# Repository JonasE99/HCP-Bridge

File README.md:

# HCP-Bridge – Hörmann series 4 garage doors on Wi-Fi / Loxone

> **⚠ Work in progress – rev 0.1 has not been manufactured or tested yet.**
> Schematic and layout are complete and checked (ERC 0 errors, DRC 0 errors), but no board has
> been built or run on an operator so far. Build at your own risk; results of the first build
> will be added here.

A small board (one per door) that plugs into the **BUS port** (RJ12) of a Hörmann series 4
garage door operator (ProMatic 4, SupraMatic E/P 4). It acts as a UAP1-HCP expansion module
towards the operator and exposes the door via Wi-Fi. Loxone talks to it over plain HTTP, no
extra server needed (see below).

**Firmware:** This repository contains the hardware only. The board is meant to run the existing
third-party open-source firmware **[HCPBridgeMqtt by Gifford47](https://github.com/Gifford47/HCPBridgeMqtt)**
(environment `HCP_Giffordv2`, provides web UI, HTTP API and MQTT). The board uses the same pins
as the original ESP32-S3 boards, so the firmware runs unchanged. Please direct firmware questions
to that project.

**Status rev 0.1 (2026-10-14):** ERC 0 errors, DRC 0 errors (4 warnings: footprint silkscreen at
the board edge, trimmed by the manufacturer).

## Key data

| | |
|---|---|
| Size | 36 × 72 mm, 2 layers, 1.6 mm, 2 × M3 |
| Power | from the bus (24 V, approx. 20–40 mA) or USB-C (5 V) |
| Radio | ESP32-S3-WROOM-1-N8R2 (PCB antenna at the top edge, no copper underneath) |
| RS-485 | TI THVD1406, automatic direction control via TX (the firmware uses TX/RX only) |
| Protection | 200 mA PTC fuse, TVS SMAJ33CA, SM712 + 10 Ω on A/B, ESD protection on USB |
| Regulator | TI LMR51610 (4–65 V, 1 A) to 3.3 V, laid out following the TI layout guidelines |
| Pins | RS-485 TX = GPIO17, RX = GPIO18, status LED = GPIO13 (as `HCP_Giffordv2`) |

### Reverse polarity and cable tolerant

RJ12 cables exist as straight and crossed versions, and the pin 1 side of the jack was derived
from documentation. Reversed, +24 V would end up on GND and A/B would be swapped. Therefore:
- Power goes through a **bridge rectifier** (4 × Schottky): polarity does not matter and the
  board is not damaged either way.
- **Solder jumpers A/B** (JP1/JP2), default 1-2 (A = jack pin 4, B = pin 3).
- **JP3 "120R"** (bus termination): leave open, close only if communication is unreliable.

**Setting A/B – one measurement is enough:** cable and jack can only swap the wires mirrored
(1↔6, 2↔5, 3↔4), so power and data always flip together. With the bridge plugged in and the
operator powered, measure on the **bottom side at the solder pins of the RJ12 jack J1**: red probe
on the pin marked **"+"** (pin 5, outer pin), black probe on the pin marked **"−"** (pin 1, outer
pin on the other end):

| Reading at J1 (+ against −) | JP1 and JP2 |
|---|---|
| approx. **+24 V** | keep at **1-2** (default) |
| approx. **−24 V** | resolder **both to 2-3** |

The rule is also printed on the bottom side. Bus pinout at the operator according to
HCPBridgeMqtt: 1/2 GND, 3 B−, 4 A+, 5/6 +24 V.

## Folders

```
hardware/kicad/        KiCad 9 project HCPBridge.kicad_pro (schematic, PCB, own footprints)
hardware/fabrication/  schematic PDF, Gerber ZIP, BOM, LCSC order file, JLCPCB BOM + CPL, assembly drawing, ERC/DRC
docs/                  board render
```

## Ordering (2 doors → 2 boards, plan a spare)

- **PCB:** upload `hardware/fabrication/HCPBridge-gerber.zip` to JLCPCB (2 layers, 1.6 mm,
  lead-free HASL; 5 pcs is the minimum).
- **Parts:** at [lcsc.com](https://www.lcsc.com) open **BOM Tool → Upload BOM File** and upload
  `hardware/fabrication/lcsc-order.xlsx` (or `lcsc-order.csv`). When asked to assign the columns,
  choose `LCSC Part Number` → LCSC Part Number and `Quantity` → Quantity. **`Quantity` is the
  quantity per board**; enter the number of boards (e.g. 3 = 2 doors + 1 spare) as the order
  multiplier in the BOM tool. The column `Total for 3 boards + spare` is for checking only (it
  adds 5 spare pieces of each small 0603 part, which tend to get lost when hand soldering), do
  not assign it. LCSC rounds up to its minimum order quantities. `bom.csv` is the per-board list
  with reference designators. Solder jumpers and test points are copper only.
- **JLCPCB assembly (alternative to hand soldering):** upload `jlcpcb-bom.csv` (BOM) and
  `jlcpcb-cpl.csv` (pick and place) in the PCB assembly step. Rotations and reference points were
  derived from the LCSC/EasyEDA footprints. Check D8, F1, L1 and U1 in the JLC placement preview:
  their EasyEDA data could not be compared (pin 1 of D8/U1 must match the marking on the board).
  J1 (RJ12) is a through-hole part; select it only if you also order through-hole assembly.
- **Optional:** order a stencil from JLCPCB as well, it makes USB-C and the ESP32 module much
  easier.
- **Cable:** RJ12 6P6C cable with **all 6 wires populated** (many phone cables only have 4!).
  Straight or crossed does not matter, the solder jumpers take care of it.

## Assembly and first start

1. Populate the regulator first (U1, L1, C1–C5, R1–R4, D7) and power it from USB-C: green LED on,
   3.3 V across C4. Then the rest. Assembly drawing: `hardware/fabrication/assembly.pdf`.
2. Flash the firmware with PlatformIO (guide:
   [flashing_instructions.md](https://github.com/Gifford47/HCPBridgeMqtt/blob/master/docs/flashing_instructions.md)),
   environment **`HCP_Giffordv2`** (ESP32-S3, TX 17 / RX 18, LED 13, PSRAM). Connect USB-C to the
   PC; if the ESP32 is not detected: hold BOOT, press RESET.
3. The bridge opens a hotspot; enter your Wi-Fi at `http://192.168.4.1`, then assign a **fixed
   IP** in your router. Set a password in the web UI (see Loxone).
4. **Unplug USB**, plug the bridge into the BUS port of the operator with the RJ12 cable.
5. **Measure at J1** (bottom side, "+"/"−") and set the A/B jumpers accordingly (see above).
   Unplug the RJ12 cable before resoldering.
6. Start a **bus scan** on the operator (otherwise it does not see the bridge): depending on the
   control board via menu 37 or by switching the last DIP switch ON → OFF. Guide:
   [bus_scan_EN.md](https://github.com/Gifford47/HCPBridgeMqtt/blob/master/docs/bus_scan_EN.md).
   The door state must then show up in the web UI.

Do not connect USB (PC) and the bus at the same time if PC and operator are earthed differently.

## Loxone integration (HTTP, no MQTT)

The commands are simple GET requests. With a web password set, the bridge asks for basic auth
(user `admin`); in Loxone use the address `http://admin:<password>@<ip>`.

**Virtual output** "Garage door 1", address `http://admin:<pw>@192.168.x.y`, commands:

| Command | Request on ON |
|---|---|
| Open | `/command?action=1` |
| Close | `/command?action=0` |
| Stop | `/command?action=2` |
| Toggle (impulse) | `/command?action=8` |
| Half open | `/command?action=4` |
| Venting | `/command?action=3` |
| Toggle light | `/command?action=5` |
| Position (0–100) | `/command?action=7&position=<v>` (analog) |

**Virtual HTTP input** "Garage door 1 status", URL `http://admin:<pw>@192.168.x.y/status`, polling
every 2–5 s. Command recognition:

| Value | Command recognition | Meaning |
|---|---|---|
| Position | `"currentPosition":\v` | 0 = closed … 100 = open |
| State | `"state":\v` | 0 open, 1 opening, 2 closed, 3 closing, 4 half open, 5/6 venting, 7 moving to half, 8 stopped |
| Light | `"light":\v` | 1 = on (true) |
| Bus OK | `"valid":\v` | 1 = operator responds |

**Gate block:** set the Loxone "Gate" block to "subsequent control" and connect its outputs Op/Cl
(or Tg) to the Open/Close (or Toggle) commands of the virtual output. Feedback comes from the HTTP
input: end position open = state 0, end position closed = state 2, the position directly from
`currentPosition` / 100. The exact inputs and outputs of the block are described in the Loxone
documentation: <https://www.loxone.com/enen/kb/gate/>. Please double-check in Loxone Config; this
mapping has not been tested on a real Miniserver yet.

## Credits and sources

- Firmware and protocol: [Gifford47/HCPBridgeMqtt](https://github.com/Gifford47/HCPBridgeMqtt),
  [Tysonpower/HCPBridgeMqtt_tynet](https://github.com/Tysonpower/HCPBridgeMqtt_tynet)
- Datasheets: [THVD1406](https://www.ti.com/lit/ds/symlink/thvd1406.pdf),
  [LMR51610](https://www.ti.com/lit/ds/symlink/lmr51610.pdf)
- RJ12 hole pattern (Molex 95501-2661): taken from the Gerber files of the board by vladimirzrnic
  in the HCPBridgeMqtt repository (`docs/PCB/vladimirzrnic`)

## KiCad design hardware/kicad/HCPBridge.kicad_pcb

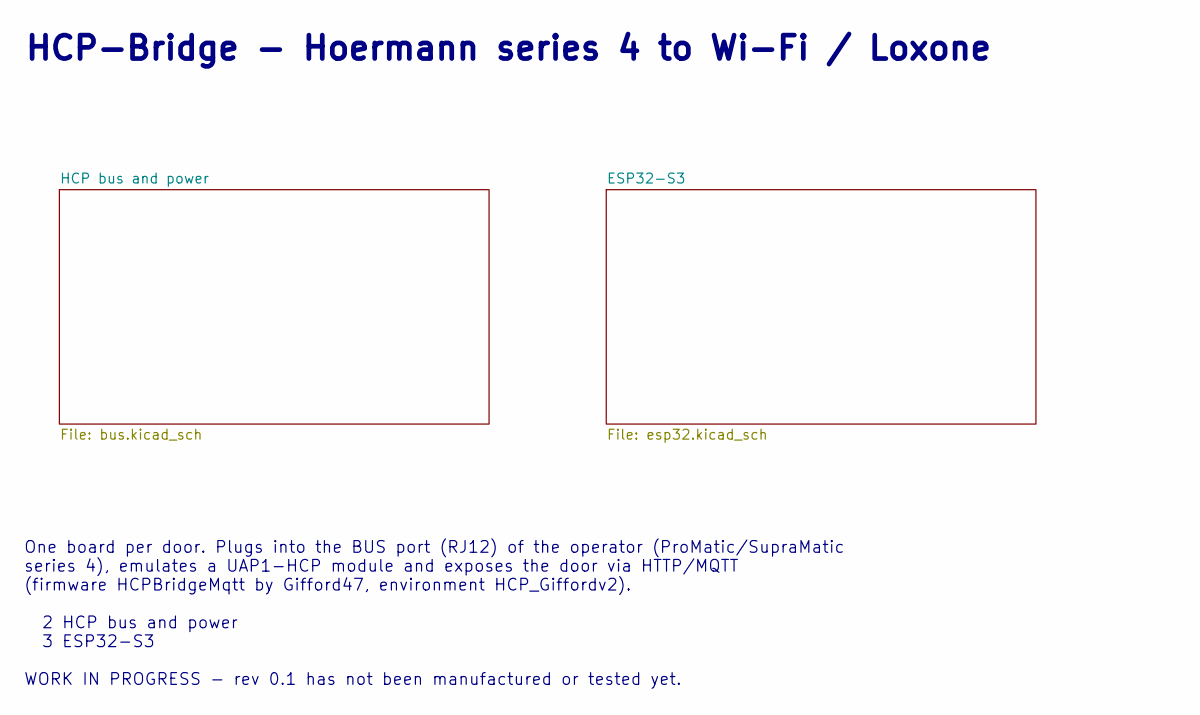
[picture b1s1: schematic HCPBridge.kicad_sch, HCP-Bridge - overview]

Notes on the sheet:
HCP-Bridge - Hoermann series 4 to Wi-Fi / Loxone
One board per door. Plugs into the BUS port (RJ12) of the operator (ProMatic/SupraMatic series 4), emulates a UAP1-HCP module and exposes the door via HTTP/MQTT (firmware HCPBridgeMqtt by Gifford47, environment HCP_Giffordv2). 2 HCP bus and power 3 ESP32-S3 WORK IN PROGRESS - rev 0.1 has not been m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

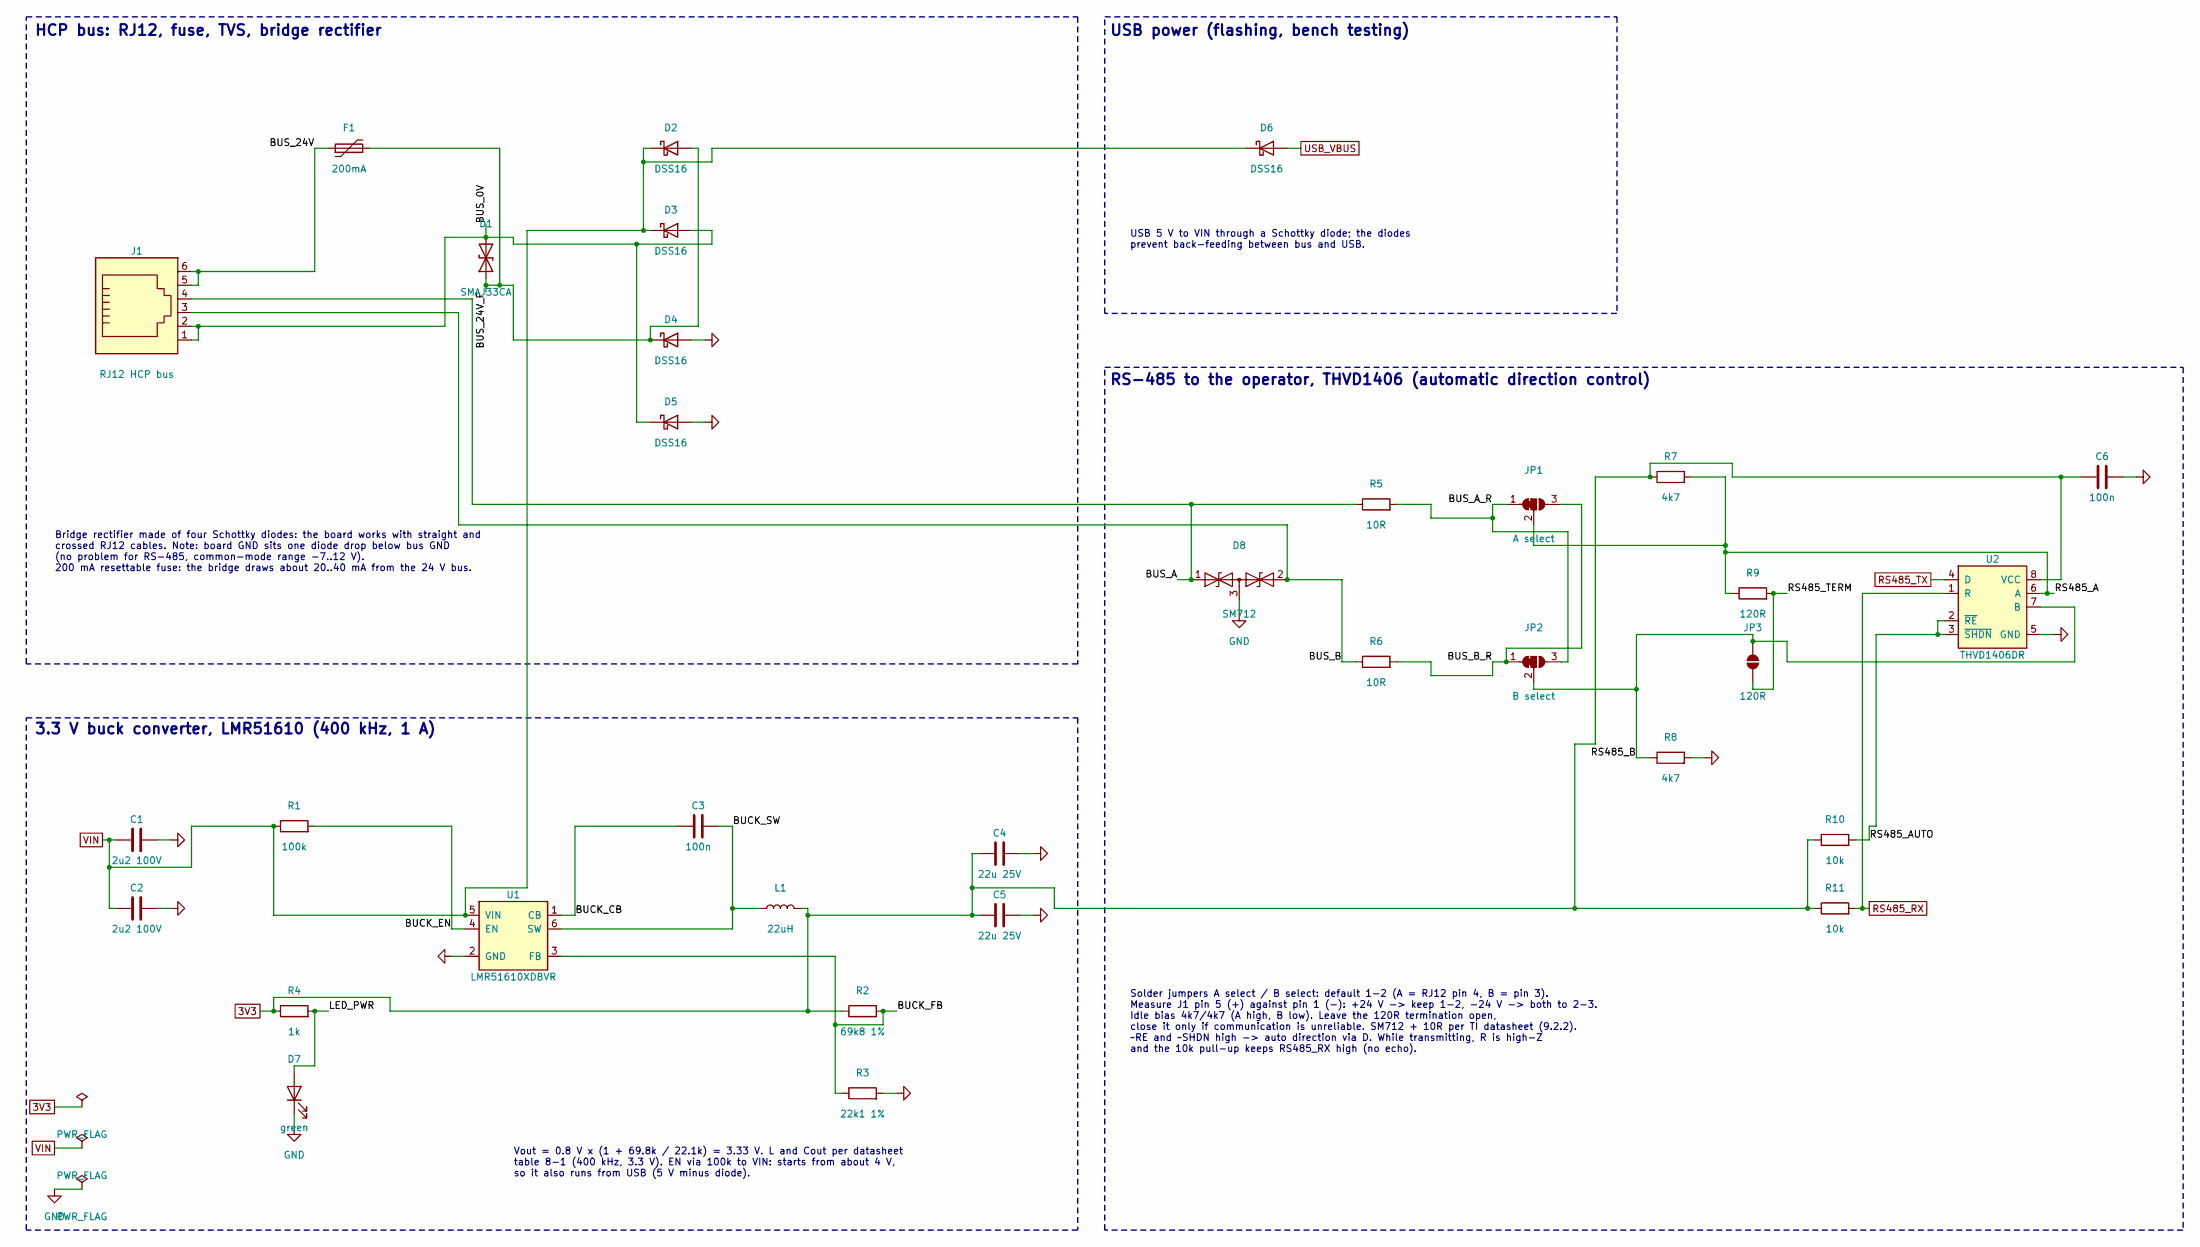
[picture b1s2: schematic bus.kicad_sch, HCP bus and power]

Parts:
C1, C2: 2u2 100V; C_1206_3216Metric; LCSC C170101
C3, C6: 100n; C_0603_1608Metric; LCSC C14663
C4, C5: 22u 25V; C_1206_3216Metric; LCSC C77091
D1: SMAJ33CA; D_SMA; MPN SMAJ33CA (bidirectional); LCSC C115251
D2, D3, D4, D5, D6: DSS16; D_SOD-123; MPN DSS16 (60 V, 1 A); LCSC C7467023
D7: green; LED_0603_1608Metric; MPN KT-0603G; LCSC C12624
D8: SM712; SOT-23; MPN Semtech SM712.TCT; LCSC C12067
F1: 200mA; Fuse_1206_3216Metric; MPN BSMD1206-020-48V; LCSC C49328459
J1: RJ12 HCP bus; RJ12_Molex_95501-2661_Horizontal; MPN Molex 95501-2661; LCSC C240856
JP1: A select; SolderJumper-3_P1.3mm_Bridged12_RoundedPad1.0x1.5mm
JP2: B select; SolderJumper-3_P1.3mm_Bridged12_RoundedPad1.0x1.5mm
JP3: 120R; SolderJumper-2_P1.3mm_Open_RoundedPad1.0x1.5mm
L1: 22uH; L_Sunlord_SWPA5040S; MPN Bourns SRN5040TA-220M (Isat 1.62 A); LCSC C2046438
R1: 100k; R_0603_1608Metric; MPN 0603WAF1003T5E; LCSC C25803
R2: 69k8 1%; R_0603_1608Metric; LCSC C23098
R3: 22k1 1%; R_0603_1608Metric; LCSC C137768
R4: 1k; R_0603_1608Metric; MPN 0603WAF1001T5E; LCSC C21190
R5, R6: 10R; R_0603_1608Metric; LCSC C22859
R7, R8: 4k7; R_0603_1608Metric; MPN 0603WAF4701T5E; LCSC C23162
R9: 120R; R_0603_1608Metric; LCSC C22787
R10, R11: 10k; R_0603_1608Metric; MPN Yageo RC0603FR-0710KL; LCSC C98220
U1: LMR51610XDBVR; SOT-23-6; MPN TI LMR51610XDBVR; LCSC C20539658
U2: THVD1406DR; SOIC-8_3.9x4.9mm_P1.27mm; MPN TI THVD1406DR; LCSC C5215918

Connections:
3V3: C4.1, C5.1, C6.1, L1.2, R2.1, R4.1, R7.1, R10.1, R11.1, U2.8 (VCC); also elsewhere on the board
BUCK_CB: C3.1, U1.1 (CB)
BUCK_EN: R1.2, U1.4 (EN)
BUCK_FB: R2.2, R3.1, U1.3 (FB)
BUCK_SW: C3.2, L1.1, U1.6 (SW)
BUS_0V: D1.2 (A2), D3.2 (A), D5.1 (K), J1.1, J1.2
BUS_24V: F1.1, J1.5, J1.6
BUS_24V_F: D1.1 (A1), D2.2 (A), D4.1 (K), F1.2
BUS_A: D8.1 (A1), J1.4, R5.1
BUS_A_R: JP1.1 (A), JP2.3 (B), R5.2
BUS_B: D8.2 (A2), J1.3, R6.1
BUS_B_R: JP1.3 (B), JP2.1 (A), R6.2
GND: C1.2, C2.2, C4.2, C5.2, C6.2, D4.2 (A), D5.2 (A), D7.1 (K), D8.3 (common), R3.2, R8.2, U1.2 (GND), U2.5 (GND); also elsewhere on the board
LED_PWR: D7.2 (A), R4.2
RS485_A: JP1.2 (C), R7.2, R9.1, U2.6 (A)
RS485_AUTO: R10.2, U2.2 (~RE), U2.3 (~SHDN)
RS485_B: JP2.2 (C), JP3.2 (B), R8.1, U2.7 (B)
RS485_RX: R11.2, U2.1 (R); also elsewhere on the board
RS485_TERM: JP3.1 (A), R9.2
RS485_TX: U2.4 (D); also elsewhere on the board
USB_VBUS: D6.2 (A); also elsewhere on the board
VIN: C1.1, C2.1, D2.1 (K), D3.1 (K), D6.1 (K), R1.1, U1.5 (VIN)

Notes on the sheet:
HCP bus: RJ12, fuse, TVS, bridge rectifier
Bridge rectifier made of four Schottky diodes: the board works with straight and crossed RJ12 cables. Note: board GND sits one diode drop below bus GND (no problem for RS-485, common-mode range -7..12 V). 200 mA resettable fuse: the bridge draws about 20..40 mA from the 24 V bus.
USB power (flashing, bench testing)
USB 5 V to VIN through a Schottky diode; the diodes prevent back-feeding between bus and USB.
3.3 V buck converter, LMR51610 (400 kHz, 1 A)
Vout = 0.8 V x (1 + 69.8k / 22.1k) = 3.33 V. L and Cout per datasheet table 8-1 (400 kHz, 3.3 V). EN via 100k to VIN: starts from about 4 V, so it also runs from USB (5 V minus diode).
RS-485 to the operator, THVD1406 (automatic direction control)
Solder jumpers A select / B select: default 1-2 (A = RJ12 pin 4, B = pin 3). Measure J1 pin 5 (+) against pin 1 (-): +24 V -> keep 1-2, -24 V -> both to 2-3. Idle bias 4k7/4k7 (A high, B low). Leave the 120R termination open, close it only if communication is unreliable. SM712 + 10R per TI datashee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

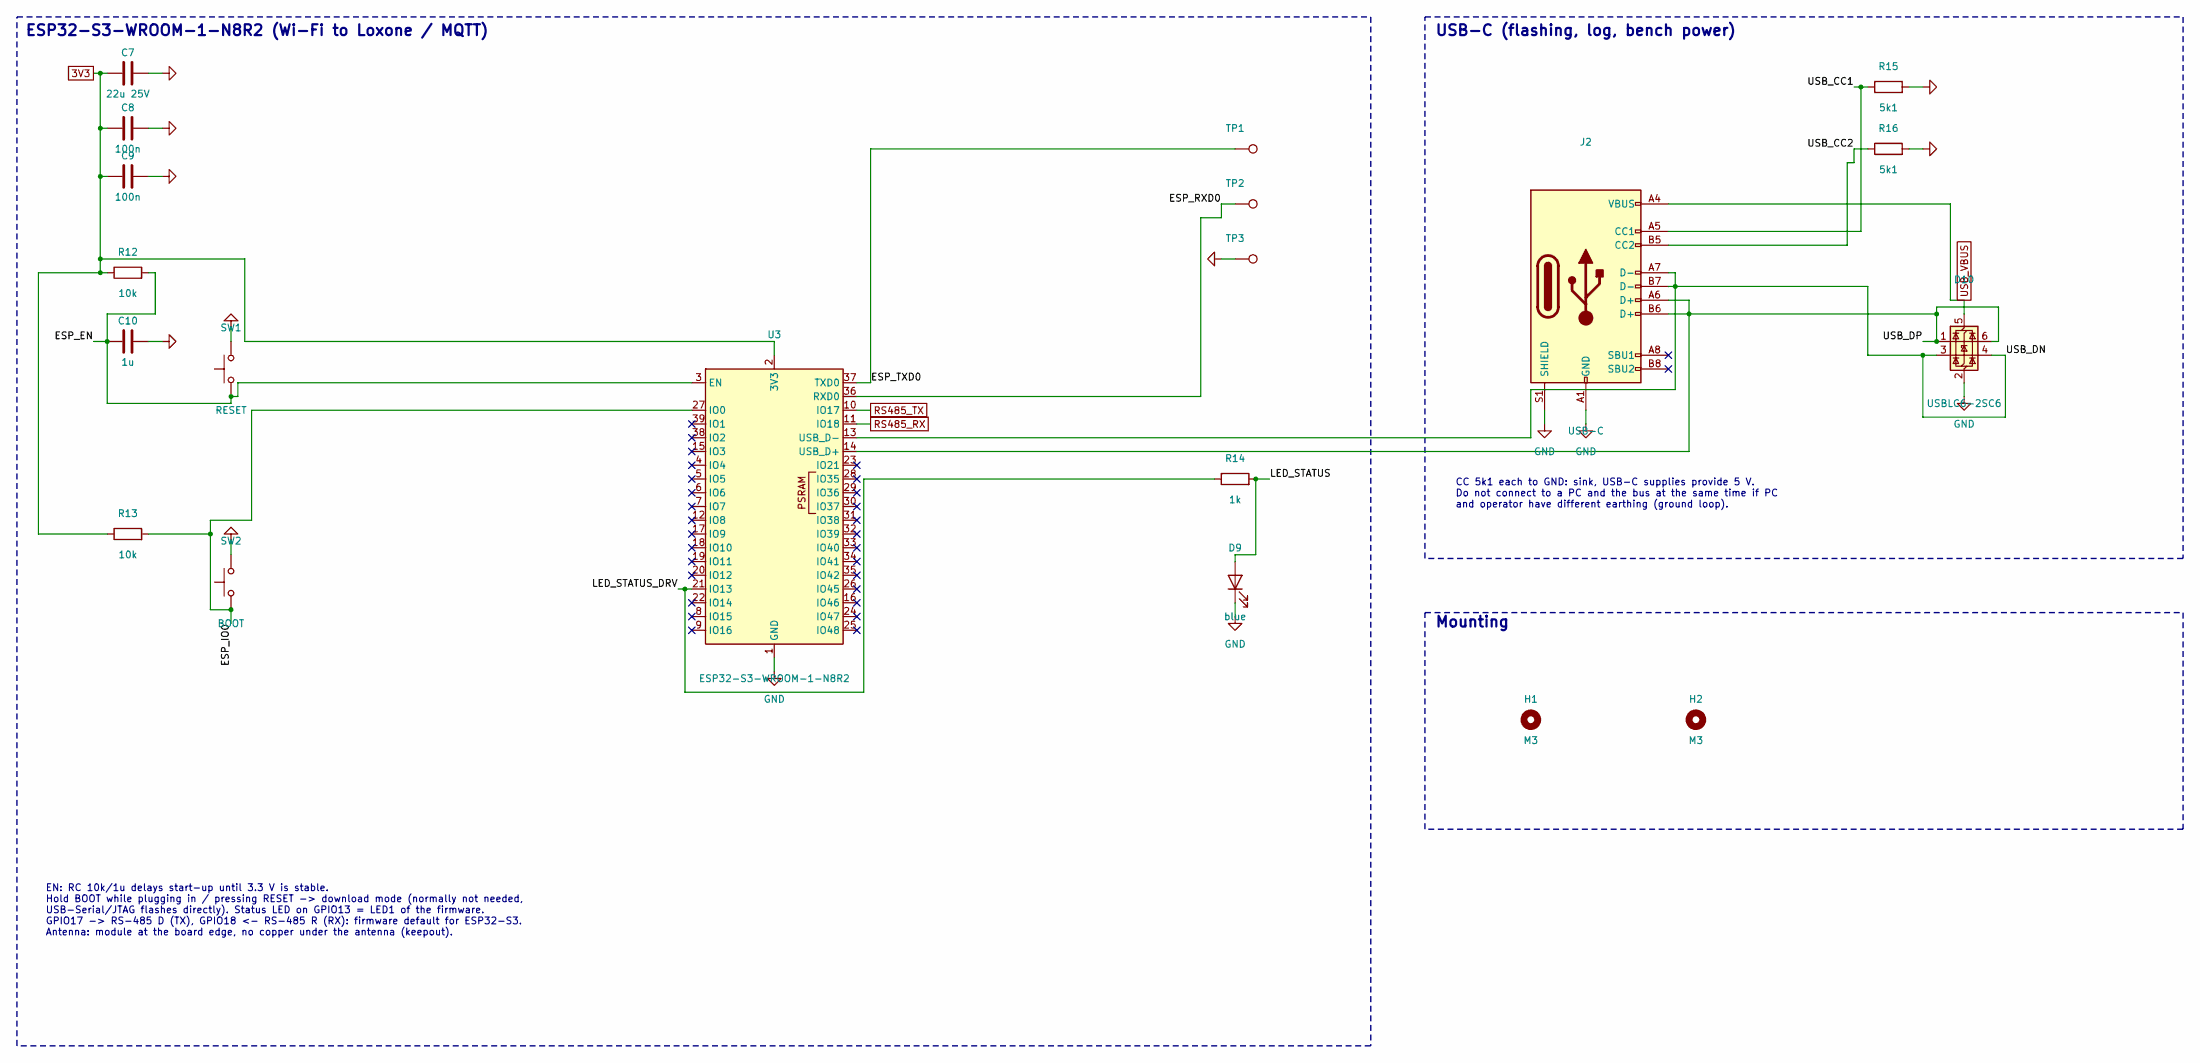
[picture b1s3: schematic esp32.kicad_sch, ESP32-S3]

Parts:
C7: 22u 25V; C_1206_3216Metric; LCSC C77091
C8, C9: 100n; C_0603_1608Metric; LCSC C14663
C10: 1u; C_0603_1608Metric; LCSC C5673
D9: blue; LED_0603_1608Metric; MPN KT-0603B; LCSC C2288
D10: USBLC6-2SC6; SOT-23-6; MPN ST USBLC6-2SC6; LCSC C7519
H1, H2: M3; MountingHole_3.2mm_M3
J2: USB-C; USB_C_Receptacle_HRO_TYPE-C-31-M-12; MPN HRO TYPE-C-31-M-12; LCSC C165948
R12, R13: 10k; R_0603_1608Metric; MPN Yageo RC0603FR-0710KL; LCSC C98220
R14: 1k; R_0603_1608Metric; MPN 0603WAF1001T5E; LCSC C21190
R15, R16: 5k1; R_0603_1608Metric; MPN 0603WAF5101T5E; LCSC C23186
SW1: RESET; SW_Push_1P1T_XKB_TS-1187A; MPN XKB TS-1187A-B-A-B; LCSC C318884
SW2: BOOT; SW_Push_1P1T_XKB_TS-1187A; MPN XKB TS-1187A-B-A-B; LCSC C318884
TP1: ESP_TXD0; TestPoint_Pad_D1.5mm
TP2: ESP_RXD0; TestPoint_Pad_D1.5mm
TP3: GND; TestPoint_Pad_D1.5mm
U3: ESP32-S3-WROOM-1-N8R2; ESP32-S3-WROOM-1; MPN Espressif ESP32-S3-WROOM-1-N8R2; LCSC C2913204

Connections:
3V3: C7.1, C8.1, C9.1, R12.1, R13.1, U3.2 (3V3); also elsewhere on the board
ESP_EN: C10.1, R12.2, SW1.1, U3.3 (EN)
ESP_IO0: R13.2, SW2.1, U3.27 (IO0)
ESP_RXD0: TP2.1, U3.36 (RXD0)
ESP_TXD0: TP1.1, U3.37 (TXD0)
GND: C7.2, C8.2, C9.2, C10.2, D9.1 (K), D10.2 (GND), J2.A1 (GND), J2.A12 (GND), J2.B1 (GND), J2.B12 (GND), J2.S1 (SHIELD), R15.2, R16.2, SW1.2, SW2.2, TP3.1, U3.1 (GND), U3.40 (GND), U3.41 (GND); also elsewhere on the board
LED_STATUS: D9.2 (A), R14.2
LED_STATUS_DRV: R14.1, U3.21 (IO13)
RS485_RX: U3.11 (IO18); also elsewhere on the board
RS485_TX: U3.10 (IO17); also elsewhere on the board
USB_CC1: J2.A5 (CC1), R15.1
USB_CC2: J2.B5 (CC2), R16.1
USB_DN: D10.3 (I/O2), D10.4 (I/O2), J2.A7 (D-), J2.B7 (D-), U3.13 (USB_D-)
USB_DP: D10.1 (I/O1), D10.6 (I/O1), J2.A6 (D+), J2.B6 (D+), U3.14 (USB_D+)
USB_VBUS: D10.5 (VBUS), J2.A4 (VBUS), J2.A9 (VBUS), J2.B4 (VBUS), J2.B9 (VBUS); also elsewhere on the board

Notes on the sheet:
ESP32-S3-WROOM-1-N8R2 (Wi-Fi to Loxone / MQTT)
EN: RC 10k/1u delays start-up until 3.3 V is stable. Hold BOOT while plugging in / pressing RESET -> download mode (normally not needed, USB-Serial/JTAG flashes directly). Status LED on GPIO13 = LED1 of the firmware. GPIO17 -> RS-485 D (TX), GPIO18 <- RS-485 R (RX): firmware default for ESP32-S3. A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
USB-C (flashing, log, bench power)
CC 5k1 each to GND: sink, USB-C supplies provide 5 V. Do not connect to a PC and the bus at the same time if PC and operator have different earthing (ground loop).
Mounting

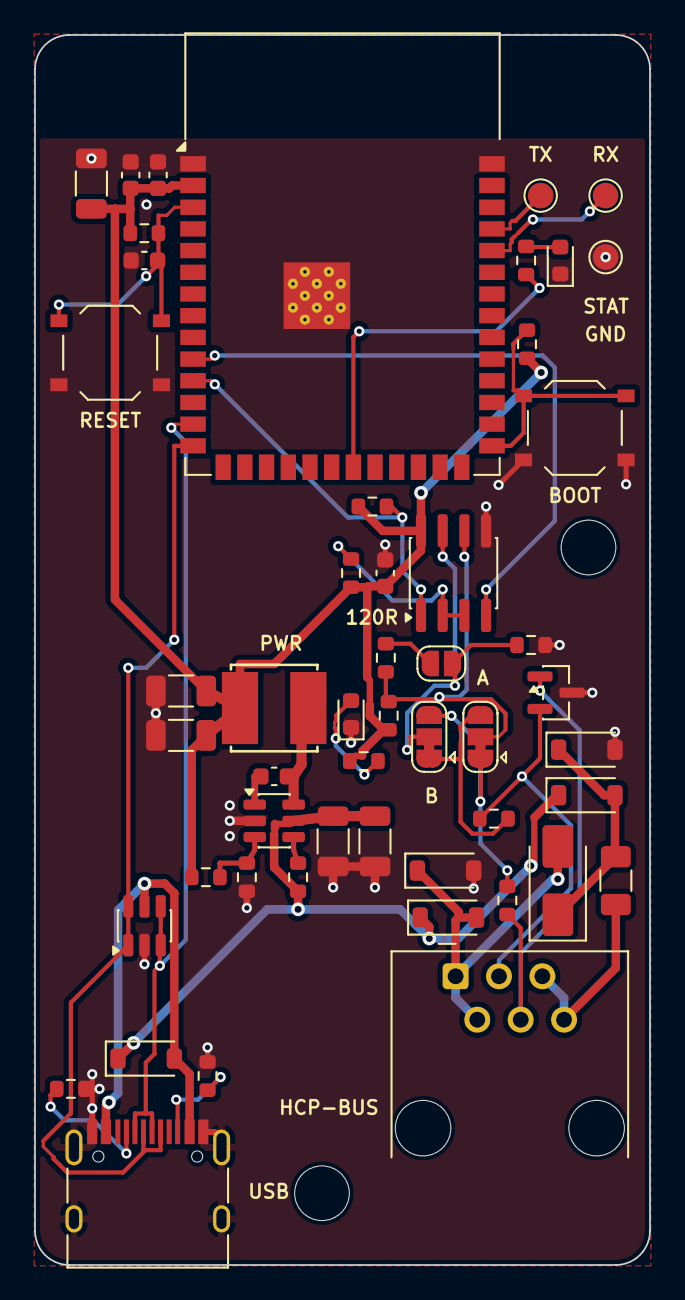
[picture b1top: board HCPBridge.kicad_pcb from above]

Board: 2 copper layers, 36.0 x 72.0 mm, 53 parts (0 on the bottom side), 32 nets.

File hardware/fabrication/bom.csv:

Qty;References;Value;Footprint;Manufacturer part;LCSC
4;C3 C6 C8 C9;100n;C_0603_1608Metric;;C14663
1;C10;1u;C_0603_1608Metric;;C5673
3;C4 C5 C7;22u 25V;C_1206_3216Metric;;C77091
2;C1 C2;2u2 100V;C_1206_3216Metric;;C170101
5;D2 D3 D4 D5 D6;DSS16;D_SOD-123;DSS16 (60 V, 1 A);C7467023
1;D8;SM712;SOT-23;Semtech SM712.TCT;C12067
1;D1;SMAJ33CA;D_SMA;SMAJ33CA (bidirectional);C115251
1;D10;USBLC6-2SC6;SOT-23-6;ST USBLC6-2SC6;C7519
1;D9;blue;LED_0603_1608Metric;KT-0603B;C2288
1;D7;green;LED_0603_1608Metric;KT-0603G;C12624
1;F1;200mA;Fuse_1206_3216Metric;BSMD1206-020-48V;C49328459
1;JP3;120R;SolderJumper-2_P1.3mm_Open_RoundedPad1.0x1.5mm;;
1;JP1;A select;SolderJumper-3_P1.3mm_Bridged12_RoundedPad1.0x1.5mm;;
1;JP2;B select;SolderJumper-3_P1.3mm_Bridged12_RoundedPad1.0x1.5mm;;
1;J1;RJ12 HCP bus;RJ12_Molex_95501-2661_Horizontal;Molex 95501-2661;C240856
1;J2;USB-C;USB_C_Receptacle_HRO_TYPE-C-31-M-12;HRO TYPE-C-31-M-12;C165948
1;L1;22uH;L_Sunlord_SWPA5040S;Bourns SRN5040TA-220M (Isat 1.62 A);C2046438
1;R1;100k;R_0603_1608Metric;0603WAF1003T5E;C25803
2;R5 R6;10R;R_0603_1608Metric;;C22859
4;R10 R11 R12 R13;10k;R_0603_1608Metric;Yageo RC0603FR-0710KL;C98220
1;R9;120R;R_0603_1608Metric;;C22787
2;R4 R14;1k;R_0603_1608Metric;0603WAF1001T5E;C21190
1;R3;22k1 1%;R_0603_1608Metric;;C137768
2;R7 R8;4k7;R_0603_1608Metric;0603WAF4701T5E;C23162
2;R15 R16;5k1;R_0603_1608Metric;0603WAF5101T5E;C23186
1;R2;69k8 1%;R_0603_1608Metric;;C23098
1;SW2;BOOT;SW_Push_1P1T_XKB_TS-1187A;XKB TS-1187A-B-A-B;C318884
1;SW1;RESET;SW_Push_1P1T_XKB_TS-1187A;XKB TS-1187A-B-A-B;C318884
1;TP2;ESP_RXD0;TestPoint_Pad_D1.5mm;;
1;TP1;ESP_TXD0;TestPoint_Pad_D1.5mm;;
1;TP3;GND;TestPoint_Pad_D1.5mm;;
1;U3;ESP32-S3-WROOM-1-N8R2;ESP32-S3-WROOM-1;Espressif ESP32-S3-WROOM-1-N8R2;C2913204
1;U1;LMR51610XDBVR;SOT-23-6;TI LMR51610XDBVR;C20539658
1;U2;THVD1406DR;SOIC-8_3.9x4.9mm_P1.27mm;TI THVD1406DR;C5215918
